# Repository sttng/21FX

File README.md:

<center></center>
# 21FX - An SNES Primary Bootloader (formerly SNES-Hook) 
This project includes Altium and verilog design files for an SNES CPLD 
expansion port to perform a simple reset hijacking and present a primary 
bootloader for the SNES to use. The bootloader is intended to be used in
conjunction with byuu's Controller Port Serial Cable for uploading
executable code into WRAM.

Updates
---------------------------------------------------------------------
4/14/2016 - REV C boards back and tested working. The boards now conform
to the new SNES expansion bridge DB-25 connector. byuu has produced the IPLROM
which is programmed to the EEPROM. Couple of issues with some power off noise
to the 232H but nothing serious

21FX - Rev C (Full Release)
---------------------------------------------------------------------
In this release we have changed the entire form factor of the board.
The board now conforms to a DB-25 connector and will mate to the new
SNES expansion bridge. We have also kept the same size CPLD and decided
to keep the IPLROM on a separate microchip 5v parallel eeprom chip. Lastly
the project no longer targets byuu's USART board. It instead has the connector
footprint for the Adafruit FT232H USB transceiver board. The IPLROM targets
all back and forth communication through this device.

SNES-Hook v1.1 REV B (Full Release)
---------------------------------------------------------------------
Updated top verilog file to include 2 more force/glitch outputs for
providing extra current strength on the glitched lines.

SNES-Hook v1.0 (Full Release)
---------------------------------------------------------------------
This a preliminary full release of SNES-Hook. In the release is the 
verilog files, Altium board design files and the quartus project which 
targets the MAX7000S CPLD on the SNES-Hook board.

@defparam

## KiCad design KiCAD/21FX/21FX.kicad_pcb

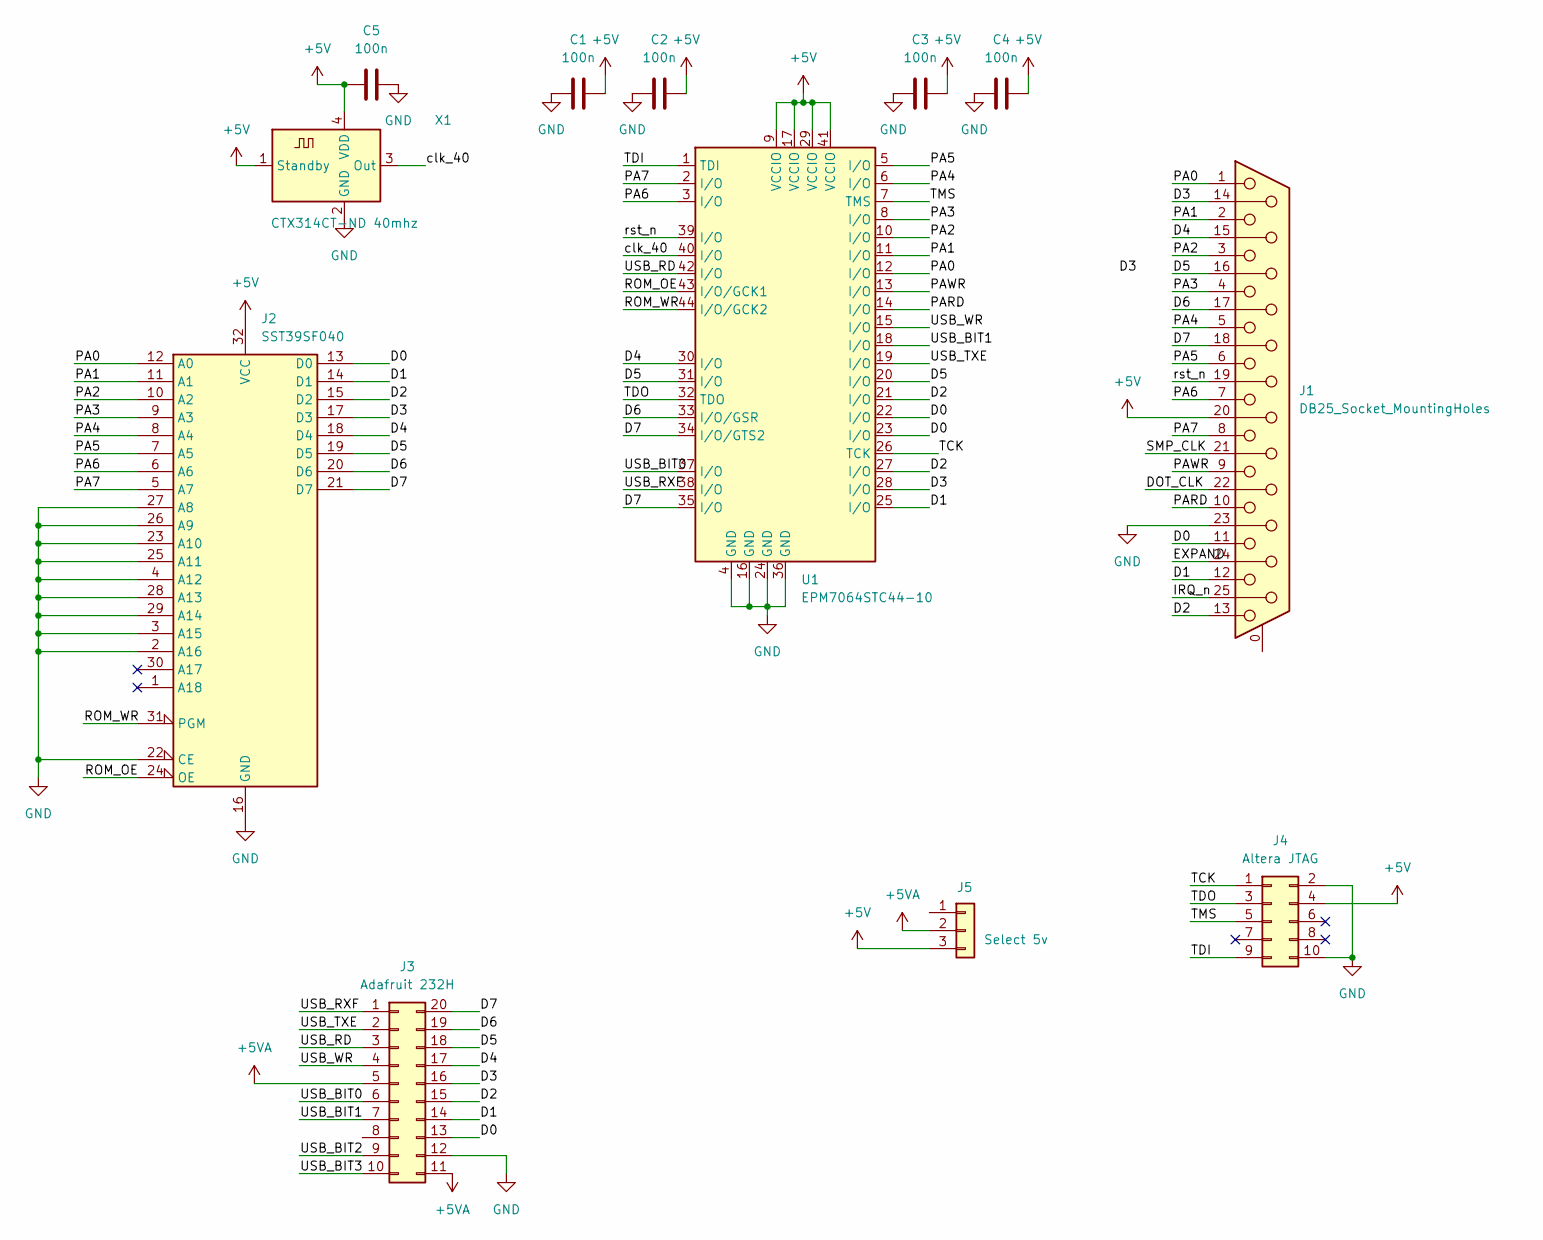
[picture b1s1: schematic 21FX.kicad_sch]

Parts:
C1, C2, C3, C4, C5: 100n; C_0805_2012Metric_Pad1.18x1.45mm_HandSolder
J1: DB25_Socket_MountingHoles; DSUB-25_Pins_Horizontal_P2.77x2.84mm_EdgePinOffset4.94mm_Ho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
J2: SST39SF040; PLCC-32_THT-Socket
J3: Adafruit 232H; PinHeader_2x10_P2.54mm_Vertical
J4: Altera JTAG; PinHeader_2x05_P2.54mm_Vertical
J5: Select 5v; PinHeader_1x03_P2.54mm_Vertical
U1: EPM7064STC44-10; TQFP-44_10x10mm_P0.8mm
X1: CTX314CT-ND 40mhz; Oscillator_SMD_Abracon_ASV-4Pin_7.0x5.1mm

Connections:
+5V: C1.2, C2.2, C3.2, C4.2, C5.1, J1.20, J2.32 (VCC), J4.4, J5.3, U1.9 (VCCIO), U1.17 (VCCIO), U1.29 (VCCIO), U1.41 (VCCIO), X1.1 (Standby), X1.4 (VDD)
+5VA: J3.5, J3.11, J5.2
/D0: J1.11, J2.13 (D0), J3.13, U1.22 (I/O), U1.23 (I/O)
/D1: J1.12, J2.14 (D1), J3.14, U1.25 (I/O)
/D2: J1.13, J2.15 (D2), J3.15, U1.21 (I/O), U1.27 (I/O)
/D3: J1.14, J2.17 (D3), J3.16, U1.28 (I/O)
/D4: J1.15, J2.18 (D4), J3.17, U1.30 (I/O)
/D5: J1.16, J2.19 (D5), J3.18, U1.20 (I/O), U1.31 (I/O)
/D6: J1.17, J2.20 (D6), J3.19, U1.33 (I/O/GSR)
/D7: J1.18, J2.21 (D7), J3.20, U1.34 (I/O/GTS2), U1.35 (I/O)
/DOT_CLK: J1.22
/EXPAND: J1.24
/IRQ_n: J1.25
/PA0: J1.1, J2.12 (A0), U1.12 (I/O)
/PA1: J1.2, J2.11 (A1), U1.11 (I/O)
/PA2: J1.3, J2.10 (A2), U1.10 (I/O)
/PA3: J1.4, J2.9 (A3), U1.8 (I/O)
/PA4: J1.5, J2.8 (A4), U1.6 (I/O)
/PA5: J1.6, J2.7 (A5), U1.5 (I/O)
/PA6: J1.7, J2.6 (A6), U1.3 (I/O)
/PA7: J1.8, J2.5 (A7), U1.2 (I/O)
/PARD: J1.10, U1.14 (I/O)
/PAWR: J1.9, U1.13 (I/O)
/ROM_OE: J2.24 (OE), U1.43 (I/O/GCK1)
/ROM_WR: J2.31 (PGM), U1.44 (I/O/GCK2)
/SMP_CLK: J1.21
/TCK: J4.1, U1.26 (TCK)
/TDI: J4.9, U1.1 (TDI)
/TDO: J4.3, U1.32 (TDO)
/TMS: J4.5, U1.7 (TMS)
/USB_BIT0: J3.6, U1.37 (I/O)
/USB_BIT1: J3.7, U1.18 (I/O)
/USB_BIT2: J3.9
/USB_BIT3: J3.10
/USB_RD: J3.3, U1.42 (I/O)
/USB_RXF: J3.1, U1.38 (I/O)
/USB_TXE: J3.2, U1.19 (I/O)
/USB_WR: J3.4, U1.15 (I/O)
/clk_40: U1.40 (I/O), X1.3 (Out)
/rst_n: J1.19, U1.39 (I/O)
GND: C1.1, C2.1, C3.1, C4.1, C5.2, J1.23, J2.2 (A16), J2.3 (A15), J2.4 (A12), J2.16 (GND), J2.22 (CE), J2.23 (A10), J2.25 (A11), J2.26 (A9), J2.27 (A8), J2.28 (A13), J2.29 (A14), J3.12, J4.2, J4.10, U1.4 (GND), U1.16 (GND), U1.24 (GND), U1.36 (GND), X1.2 (GND)

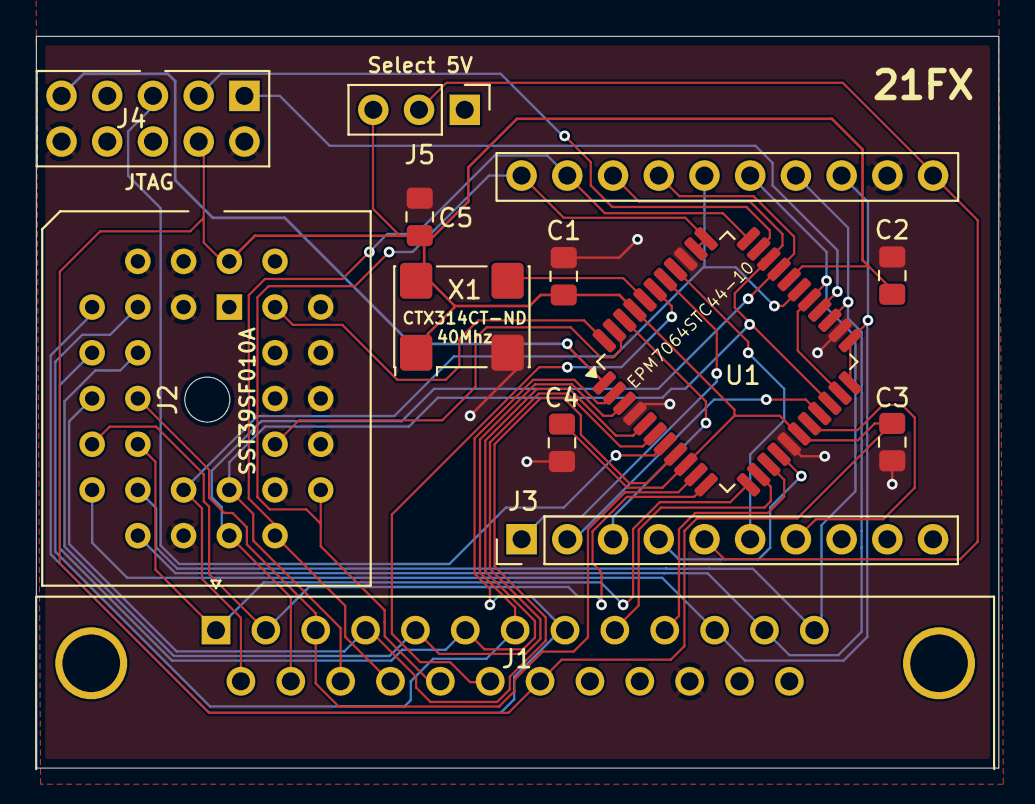
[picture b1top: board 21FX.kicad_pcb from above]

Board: 4 copper layers, 53.5 x 40.6 mm, 12 parts (0 on the bottom side), 35 nets.
